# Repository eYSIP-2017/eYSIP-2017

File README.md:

# eYSIP-2017_DistributedRobotics
## Project Title: 
Distributed Robotic - Multi Swarm Robots

## Project Description:
Understanding the behaviour of swarm robots and swarm intelligence. Building of swarm robots and displaying collective intelligence.

## Problem definition:
Using the swarm robots make the desired shapes of Alphabets. 

## Team: 
### Mentors: 
Ms. Rutuja and Ms. Deepa
### Members: 
Mr. R Hariharan and Mr. Chinmay

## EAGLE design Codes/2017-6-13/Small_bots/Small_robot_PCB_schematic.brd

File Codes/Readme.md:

# Contents of the folder
2017-5-27 : P-Controller for angular velocity of a robot (C Code)

2017-5-30 : C Code for Randezvous Problem 

2017-5-31 : Embedded C Code for Randezvous Problem (Firebird V)

2017-6-01 : Mini Bots eagle design folder and line forming algorithm C Code

2017-6-07 : Mini Bots eagle design folder - Updated

2017-6-09 : Mini Bots eagle design folder - Updated

2017-6-10 : Embedded C Code to check the properties of switching IR (Firebird V)

2017-6-13 : Mini Bots eagle design folder - Updated

2017-6-19 : V-REP documents for P-Controller for a mobile robot to goto any co-ordinate

2017-6-26 : V-REP documents for implementation of circle formation of fat robots algorithm
 
2017-6-27 : All the test codes for our Mini Robot

2017-7-05 : V-REP documents for implementation generic shape formation algorithm

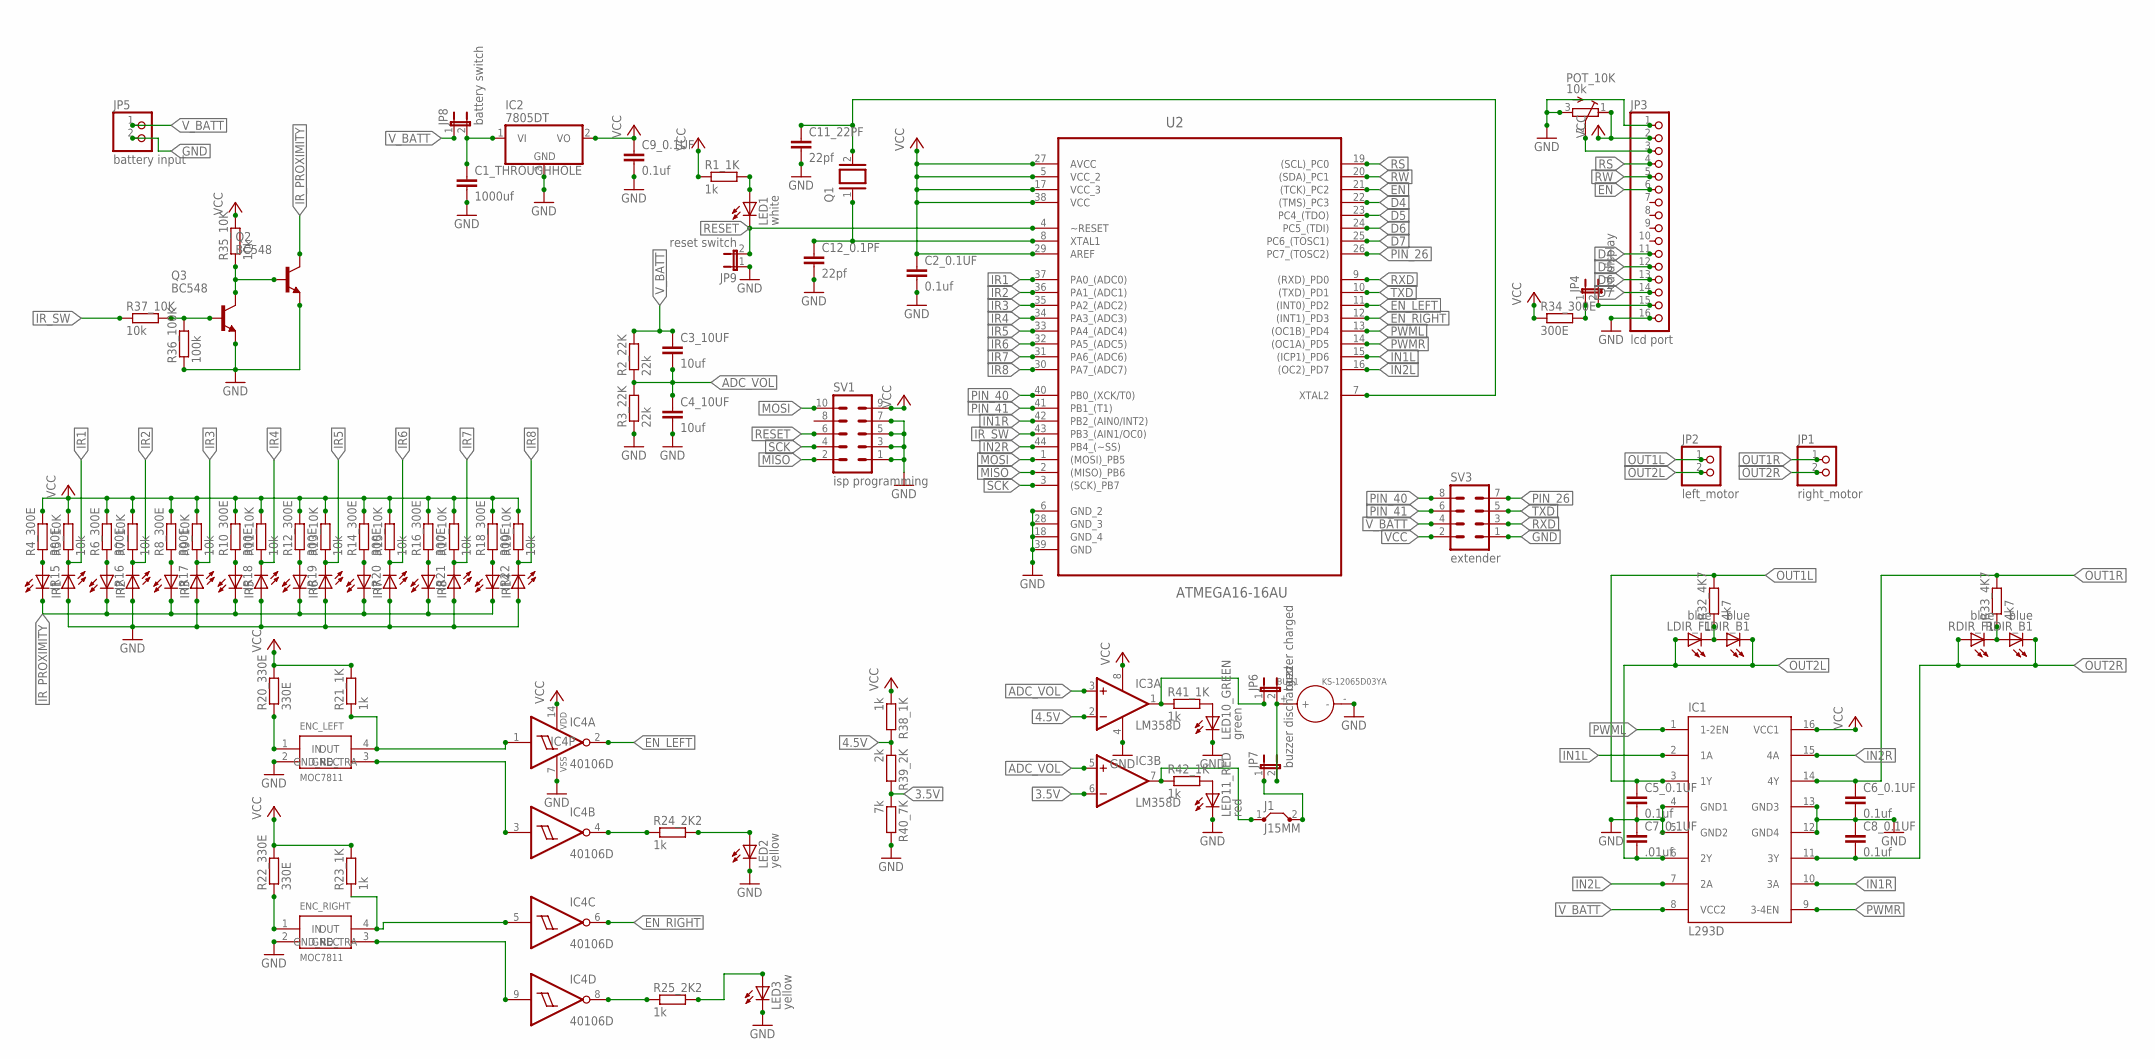
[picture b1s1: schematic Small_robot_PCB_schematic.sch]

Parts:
BUZ1: KS-12065D03YA; BZ2-7.6-D12.0XH6.5MM
C1_THROUGHHOLE: 1000uf; C050-045X075
C2_0.1UF, C5_0.1UF, C6_0.1UF, C8_0.1UF, C9_0.1UF: 0.1uf; C1206
C3_10UF, C4_10UF: 10uf; C1206
C7_0.1UF: .01uf; C1206
C11_22PF, C12_0.1PF: 22pf; C1206
ENC_LEFT: MOC7811; THROUGH_HOLE_NORMAL
ENC_RIGHT: MOC7811; THROUGH_HOLE_NORMAL
IC1: L293D; DIL16
IC2: 7805DT; TO252
IC3: LM358D; SO08
IC4: 40106D; SO14
IR1, IR2, IR3, IR5, IR6, IR7, IR8, IR14, IR15, IR16, IR17, IR18, IR19, IR20, IR21, IR22: LED5MM
J1: J15MM; 15
JP1: right_motor; 1X02
JP2: left_motor; 1X02
JP3: lcd port; 1X16
JP4: lcd display; JP1
JP5: battery input; 1X02
JP6: buzzer charged; JP1
JP7: buzzer discharged; JP1
JP8: battery switch; JP1
JP9: reset switch; JP1
LDIR_B1: blue; CHIPLED_1206
LDIR_F1: blue; CHIPLED_1206
LED1: white; CHIPLED_1206
LED2, LED3: yellow; CHIPLED_1206
LED10_GREEN: green; CHIPLED_1206
LED11_RED: red; CHIPLED_1206
POT_10K: 10k; RTRIMT93YA
Q1: XTAL; Q
Q2, Q3: BC548; TO92-EBC
R1_1K, R21_1K, R23_1K, R24_2K2, R25_2K2, R38_1K, R41_1K, R42_1K: 1k; R1206
R2_22K, R3_22K: 22k; R1206
R4_300E, R6_300E, R8_300E, R10_300E, R12_300E, R14_300E, R16_300E, R18_300E, R34_300E: 300E; R1206
R5_10K, R7_10K, R9_10K, R11_10K, R13_10K, R15_10K, R17_10K, R19_10K, R35_10K, R37_10K: 10k; R1206
R20_330E, R22_330E: 330E; R1206
R32_4K7, R33_4K7: 4k7; R1206
R36_100K: 100k; R1206
R39_2K: 2k; R1206
R40_7K: 7k; R1206
RDIR_B1: blue; CHIPLED_1206
RDIR_F1: blue; CHIPLED_1206
SV1: isp programming; MA05-2
SV3: extender; MA04-2
U2: ATMEGA16-16AU; QFP80P1200X1200X120-44N

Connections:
3.5V: IC3.6 (-IN), R39_2K.2, R40_7K.1
4.5V: IC3.2 (-IN), R38_1K.2, R39_2K.1
ADC_VOL: C3_10UF.2, C4_10UF.1, IC3.3 (+IN), IC3.5 (+IN), R2_22K.1, R3_22K.2
D4: JP3.11, U2.22 ((TMS)_PC3)
D5: JP3.12, U2.23 (PC4_(TDO))
D6: JP3.13, U2.24 (PC5_(TDI))
D7: JP3.14, U2.25 (PC6_(TOSC1))
EN: JP3.6, U2.21 ((TCK)_PC2)
EN_LEFT: IC4.2 (O), U2.11 ((INT0)_PD2)
EN_RIGHT: IC4.6 (O), U2.12 ((INT1)_PD3)
GND: BUZ1.-, C1_THROUGHHOLE.2, C2_0.1UF.2, C4_10UF.2, C5_0.1UF.2, C6_0.1UF.2, C7_0.1UF.1, C8_0.1UF.1, C9_0.1UF.2, C11_22PF.2, C12_0.1PF.2, ENC_LEFT.2 (GND_TRA), ENC_RIGHT.2 (GND_TRA), IC1.4 (GND1), IC1.5 (GND2), IC1.12 (GND4), IC1.13 (GND3), IC2.3 (GND), IC3.4 (V-), IC4.7 (VSS), IR15.A, IR16.A, IR17.A, IR18.A, IR19.A, IR20.A, IR21.A, IR22.A, JP3.1, JP3.16, JP5.2, JP9.1, LED2.C, LED3.C, LED10_GREEN.C, LED11_RED.C, POT_10K.3 (A), Q2.E, Q3.E, R3_22K.1, R36_100K.1, R40_7K.2, SV1.1, SV1.3, SV1.5, SV1.7, SV3.1, U2.6 (GND_2), U2.18 (GND_4), U2.28 (GND_3), U2.39 (GND)
IN1L: IC1.2 (1A), U2.15 ((ICP1)_PD6)
IN1R: IC1.10 (3A), U2.42 (PB2_(AIN0/INT2))
IN2L: IC1.7 (2A), U2.16 ((OC2)_PD7)
IN2R: IC1.15 (4A), U2.44 (PB4_(~SS))
IR1: IR15.K (C), R5_10K.1, U2.37 (PA0_(ADC0))
IR2: IR16.K (C), R7_10K.1, U2.36 (PA1_(ADC1))
IR3: IR17.K (C), R9_10K.1, U2.35 (PA2_(ADC2))
IR4: IR18.K (C), R11_10K.1, U2.34 (PA3_(ADC3))
IR5: IR19.K (C), R13_10K.1, U2.33 (PA4_(ADC4))
IR6: IR20.K (C), R15_10K.1, U2.32 (PA5_(ADC5))
IR7: IR21.K (C), R17_10K.1, U2.31 (PA6_(ADC6))
IR8: IR22.K (C), R19_10K.1, U2.30 (PA7_(ADC7))
IR_PROXIMITY: IR1.K (C), IR2.K (C), IR3.K (C), IR5.K (C), IR6.K (C), IR7.K (C), IR8.K (C), IR14.K (C), Q2.C
IR_SW: R37_10K.1, U2.43 (PB3_(AIN1/OC0))
MISO: SV1.2, U2.2 ((MISO)_PB6)
MOSI: SV1.10, U2.1 ((MOSI)_PB5)
N: JP3.3, POT_10K.2 (S)
unnamed: ENC_LEFT.1 (IN), R20_330E.1
unnamed: C12_0.1PF.1, Q1.1, U2.8 (XTAL1)
unnamed: C11_22PF.1, Q1.2, U2.7 (XTAL2)
unnamed: IR1.A, R4_300E.1
unnamed: IR2.A, R6_300E.1
unnamed: IR3.A, R8_300E.1
unnamed: IR5.A, R10_300E.1
unnamed: LED1.A, R1_1K.2
unnamed: IR6.A, R12_300E.1
unnamed: IR7.A, R14_300E.1
unnamed: IR8.A, R16_300E.1
unnamed: IR14.A, R18_300E.1
unnamed: Q3.B, R36_100K.2, R37_10K.2
unnamed: C1_THROUGHHOLE.1, IC2.1 (VI), JP8.2
unnamed: IC4.4 (O), R24_2K2.1
unnamed: LED2.A, R24_2K2.2
unnamed: IC4.8 (O), R25_2K2.1
unnamed: LED3.A, R25_2K2.2
unnamed: ENC_RIGHT.1 (IN), R22_330E.1
unnamed: LED10_GREEN.A, R41_1K.2
unnamed: IC3.7 (OUT), J1.1, R42_1K.1
unnamed: ENC_RIGHT.4 (OUT), IC4.5 (I), R23_1K.1
unnamed: J1.2, JP7.1
unnamed: Q2.B, Q3.C, R35_10K.1
unnamed: R33_4K7.1, RDIR_B1.A, RDIR_F1.C
unnamed: ENC_LEFT.4 (OUT), IC4.1 (I), R21_1K.1
unnamed: ENC_LEFT.3 (GND_REC), IC4.3 (I)
unnamed: ENC_RIGHT.3 (GND_REC), IC4.9 (I)
unnamed: LED11_RED.A, R42_1K.2
unnamed: BUZ1.+, JP6.2, JP7.2
unnamed: IC3.1 (OUT), JP6.1, R41_1K.1
unnamed: LDIR_B1.A, LDIR_F1.C, R32_4K7.1
unnamed: JP3.15, JP4.2
unnamed: JP4.1, R34_300E.2
OUT1L: C5_0.1UF.1, IC1.3 (1Y), JP2.1, R32_4K7.2
OUT1R: C6_0.1UF.1, IC1.14 (4Y), JP1.1, R33_4K7.2
OUT2L: C7_0.1UF.2, IC1.6 (2Y), JP2.2, LDIR_B1.C, LDIR_F1.A
OUT2R: C8_0.1UF.2, IC1.11 (3Y), JP1.2, RDIR_B1.C, RDIR_F1.A
PIN_26: SV3.7, U2.26 (PC7_(TOSC2))
PIN_40: SV3.8, U2.40 (PB0_(XCK/T0))
PIN_41: SV3.6, U2.41 (PB1_(T1))
PWML: IC1.1 (1-2EN), U2.13 ((OC1B)_PD4)
PWMR: IC1.9 (3-4EN), U2.14 ((OC1A)_PD5)
RESET: JP9.2, LED1.C, SV1.6, U2.4 (~RESET)
RS: JP3.4, U2.19 ((SCL)_PC0)
RW: JP3.5, U2.20 ((SDA)_PC1)
RXD: SV3.3, U2.9 ((RXD)_PD0)
SCK: SV1.4, U2.3 ((SCK)_PB7)
TXD: SV3.5, U2.10 ((TXD)_PD1)
VCC: C2_0.1UF.1, C9_0.1UF.1, IC1.16 (VCC1), IC2.2 (VO), IC3.8 (V+), IC4.14 (VDD), JP3.2, POT_10K.1 (E), R1_1K.1, R4_300E.2, R5_10K.2, R6_300E.2, R7_10K.2, R8_300E.2, R9_10K.2, R10_300E.2, R11_10K.2, R12_300E.2, R13_10K.2, R14_300E.2, R15_10K.2, R16_300E.2, R17_10K.2, R18_300E.2, R19_10K.2, R20_330E.2, R21_1K.2, R22_330E.2, R23_1K.2, R34_300E.1, R35_10K.2, R38_1K.1, SV1.9, SV3.2, U2.5 (VCC_2), U2.17 (VCC_3), U2.27 (AVCC), U2.29 (AREF), U2.38 (VCC)
V_BATT: C3_10UF.1, IC1.8 (VCC2), JP5.1, JP8.1, R2_22K.2, SV3.4

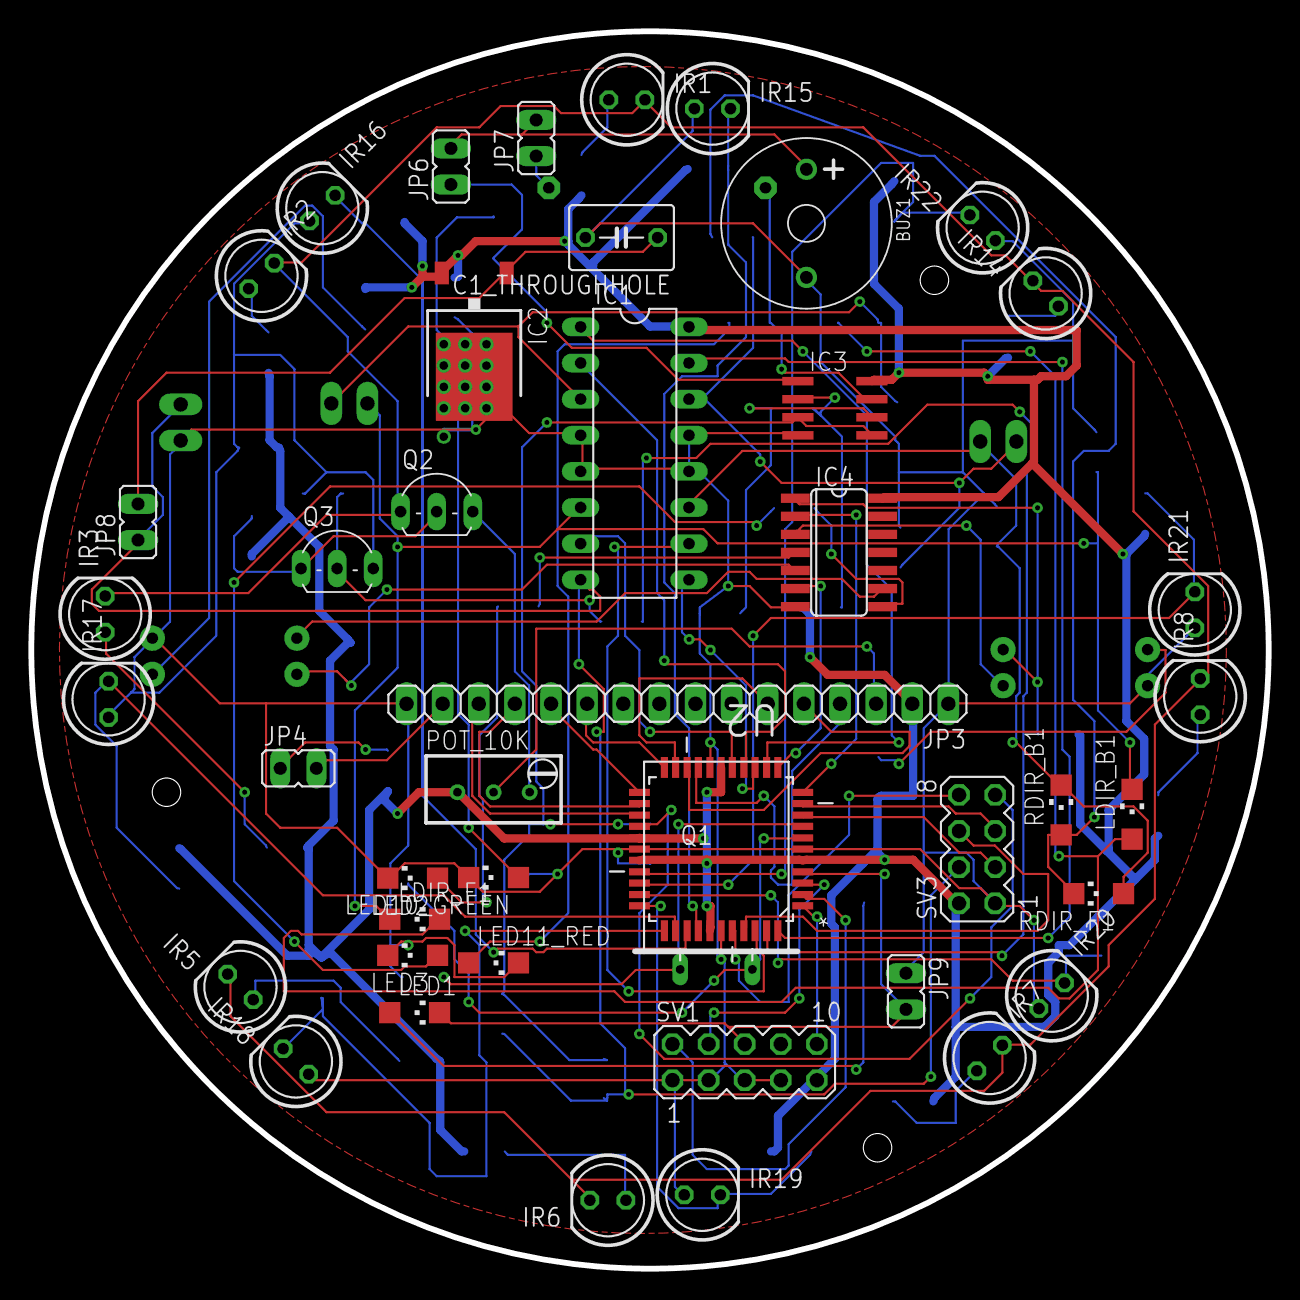
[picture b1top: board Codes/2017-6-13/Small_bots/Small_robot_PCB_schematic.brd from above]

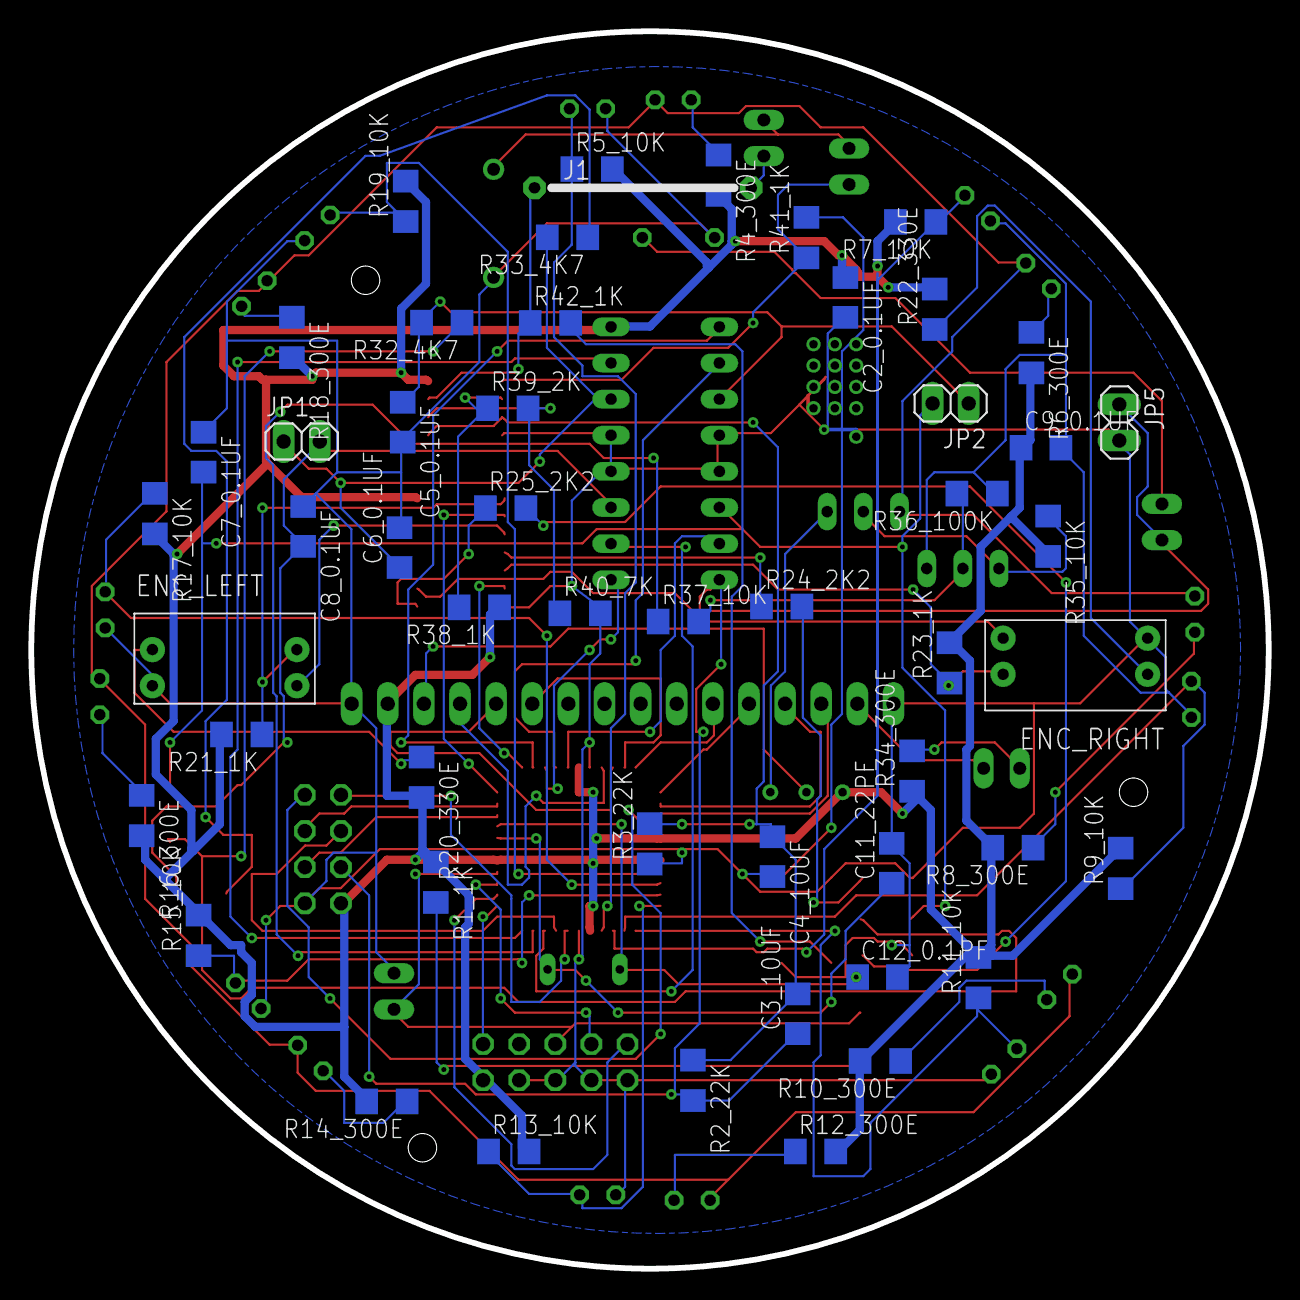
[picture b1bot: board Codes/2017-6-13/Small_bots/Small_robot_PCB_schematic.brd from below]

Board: 2 copper layers, 87.0 x 87.0 mm, 96 parts (52 on the bottom side), 79 nets.

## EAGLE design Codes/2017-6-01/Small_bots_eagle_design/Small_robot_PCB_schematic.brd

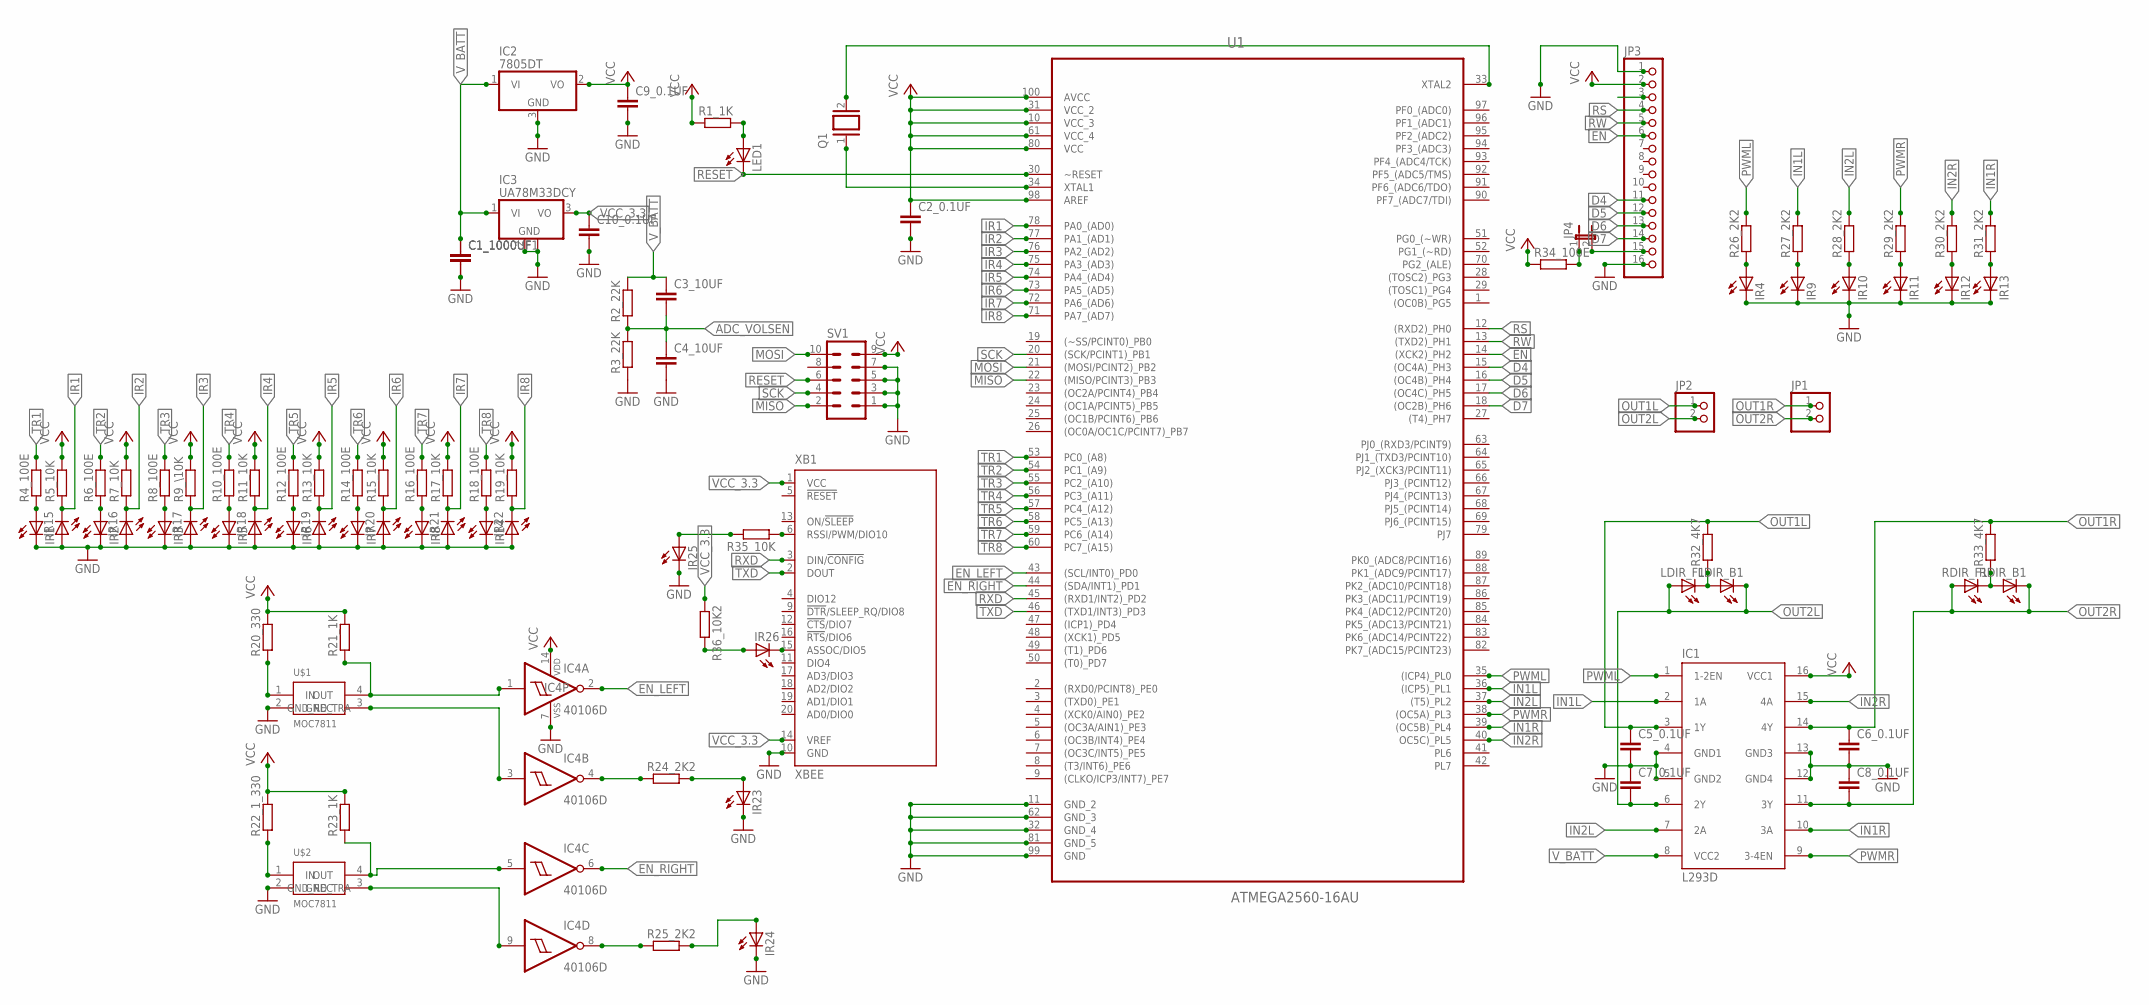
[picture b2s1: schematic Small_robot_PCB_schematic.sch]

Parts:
C1_1000UF, C1_1000UF1, C2_0.1UF, C3_10UF, C4_10UF, C5_0.1UF, C6_0.1UF, C7_0.1UF, C8_0.1UF, C9_0.1UF, C10_0.1UF: C-EUC1206; C1206
IC1: L293D; DIL16
IC2: 7805DT; TO252
IC3: UA78M33DCY; SOT223
IC4: 40106D; SO14
IR1, IR2, IR3, IR5, IR6, IR7, IR8, IR14, IR15, IR16, IR17, IR18, IR19, IR20, IR21, IR22: LED5MM
IR4, IR9, IR10, IR11, IR12, IR13, IR23, IR24, IR25, IR26: LEDCHIPLED_1206; CHIPLED_1206
JP1, JP2: PINHD-1X2; 1X02
JP3: PINHD-1X16; 1X16
JP4: JP1E; JP1
LDIR_B1: LEDCHIPLED_1206; CHIPLED_1206
LDIR_F1: LEDCHIPLED_1206; CHIPLED_1206
LED1: LEDCHIPLED_1206; CHIPLED_1206
Q1: XTAL; Q
R1_1K, R2_22K, R4_100E, R5_10K, R6_100E, R7_10K, R8_100E, R9_\10K, R10_100E, R11_10K, R12_100E, R13_10K, R14_100E, R15_10K, R16_100E, R17_10K, R18_100E, R19_10K, R20_330, R21_1K, R22_1_330, R23_1K, R24_2K2, R25_2K2, R26_2K2, R27_2K2, R28_2K2, R29_2K2, R30_2K2, R31_2K2, R32_4K7, R33_4K7, R34_100E, R35_10K, R36_10K2: R-EU_R1206; R1206
R3_22K: R-EU_M1206; M1206
RDIR_B1: LEDCHIPLED_1206; CHIPLED_1206
RDIR_F1: LEDCHIPLED_1206; CHIPLED_1206
SV1: MA05-2
U1: ATMEGA2560-16AU; QFP50P1600X1600X120-100N
U$1, U$2: MOC7811; THROUGH_HOLE_NORMAL
XB1: XBEE

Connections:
ADC_VOLSEN: C3_10UF.2, C4_10UF.1, R2_22K.1, R3_22K.2
D4: JP3.11, U1.15 ((OC4A)_PH3)
D5: JP3.12, U1.16 ((OC4B)_PH4)
D6: JP3.13, U1.17 ((OC4C)_PH5)
D7: JP3.14, U1.18 ((OC2B)_PH6)
EN: JP3.6, U1.14 ((XCK2)_PH2)
EN_LEFT: IC4.2 (O), U1.43 ((SCL/INT0)_PD0)
EN_RIGHT: IC4.6 (O), U1.44 ((SDA/INT1)_PD1)
GND: C1_1000UF.2, C1_1000UF1.2, C2_0.1UF.2, C4_10UF.2, C5_0.1UF.2, C6_0.1UF.2, C7_0.1UF.1, C8_0.1UF.1, C9_0.1UF.2, C10_0.1UF.2, IC1.4 (GND1), IC1.5 (GND2), IC1.12 (GND4), IC1.13 (GND3), IC2.3 (GND), IC3.2 (GND), IC3.4 (GND), IC4.7 (VSS), IR1.K (C), IR2.K (C), IR3.K (C), IR4.C, IR5.K (C), IR6.K (C), IR7.K (C), IR8.K (C), IR9.C, IR10.C, IR11.C, IR12.C, IR13.C, IR14.K (C), IR15.A, IR16.A, IR17.A, IR18.A, IR19.A, IR20.A, IR21.A, IR22.A, IR23.C, IR24.C, IR25.C, JP3.1, JP3.16, R3_22K.1, SV1.1, SV1.3, SV1.5, SV1.7, U1.11 (GND_2), U1.32 (GND_4), U1.62 (GND_3), U1.81 (GND_5), U1.99 (GND), U$1.2 (GND_TRA), U$2.2 (GND_TRA), XB1.10 (GND)
IN1L: IC1.2 (1A), R27_2K2.2, U1.36 ((ICP5)_PL1)
IN1R: IC1.10 (3A), R31_2K2.2, U1.39 ((OC5B)_PL4)
IN2L: IC1.7 (2A), R28_2K2.2, U1.37 ((T5)_PL2)
IN2R: IC1.15 (4A), R30_2K2.2, U1.40 (OC5C)_PL5)
IR1: IR15.K (C), R5_10K.1, U1.78 (PA0_(AD0))
IR2: IR16.K (C), R7_10K.1, U1.77 (PA1_(AD1))
IR3: IR17.K (C), R9_\10K.1, U1.76 (PA2_(AD2))
IR4: IR18.K (C), R11_10K.1, U1.75 (PA3_(AD3))
IR5: IR19.K (C), R13_10K.1, U1.74 (PA4_(AD4))
IR6: IR20.K (C), R15_10K.1, U1.73 (PA5_(AD5))
IR7: IR21.K (C), R17_10K.1, U1.72 (PA6_(AD6))
IR8: IR22.K (C), R19_10K.1, U1.71 (PA7_(AD7))
MISO: SV1.2, U1.22 ((MISO/PCINT3)_PB3)
MOSI: SV1.10, U1.21 ((MOSI/PCINT2)_PB2)
N: JP3.3
unnamed: R20_330.1, U$1.1 (IN)
unnamed: Q1.1, U1.34 (XTAL1)
unnamed: Q1.2, U1.33 (XTAL2)
unnamed: IR1.A, R4_100E.1
unnamed: IR2.A, R6_100E.1
unnamed: IR3.A, R8_100E.1
unnamed: IR5.A, R10_100E.1
unnamed: LED1.A, R1_1K.2
unnamed: IR6.A, R12_100E.1
unnamed: IR7.A, R14_100E.1
unnamed: IR8.A, R16_100E.1
unnamed: IR14.A, R18_100E.1
unnamed: IR4.A, R26_2K2.1
unnamed: IC4.4 (O), R24_2K2.1
unnamed: IR23.A, R24_2K2.2
unnamed: IC4.8 (O), R25_2K2.1
unnamed: IR24.A, R25_2K2.2
unnamed: R22_1_330.1, U$2.1 (IN)
unnamed: IR9.A, R27_2K2.1
unnamed: IR10.A, R28_2K2.1
unnamed: IC4.5 (I), R23_1K.1, U$2.4 (OUT)
unnamed: IR11.A, R29_2K2.1
unnamed: IR12.A, R30_2K2.1
unnamed: IR13.A, R31_2K2.1
unnamed: R35_10K.1, XB1.6 (RSSI/PWM/DIO10)
unnamed: R33_4K7.1, RDIR_B1.A, RDIR_F1.C
unnamed: IC4.1 (I), R21_1K.1, U$1.4 (OUT)
unnamed: IC4.3 (I), U$1.3 (GND_REC)
unnamed: IC4.9 (I), U$2.3 (GND_REC)
unnamed: IR25.A, R35_10K.2
unnamed: IR26.C, XB1.15 (ASSOC/DIO5)
unnamed: IR26.A, R36_10K2.2
unnamed: LDIR_B1.A, LDIR_F1.C, R32_4K7.1
unnamed: JP3.15, JP4.2
unnamed: JP4.1, R34_100E.2
OUT1L: C5_0.1UF.1, IC1.3 (1Y), JP2.1, R32_4K7.2
OUT1R: C6_0.1UF.1, IC1.14 (4Y), JP1.1, R33_4K7.2
OUT2L: C7_0.1UF.2, IC1.6 (2Y), JP2.2, LDIR_B1.C, LDIR_F1.A
OUT2R: C8_0.1UF.2, IC1.11 (3Y), JP1.2, RDIR_B1.C, RDIR_F1.A
PWML: IC1.1 (1-2EN), R26_2K2.2, U1.35 ((ICP4)_PL0)
PWMR: IC1.9 (3-4EN), R29_2K2.2, U1.38 ((OC5A)_PL3)
RESET: LED1.C, SV1.6, U1.30 (~RESET)
RS: JP3.4, U1.12 ((RXD2)_PH0)
RW: JP3.5, U1.13 ((TXD2)_PH1)
RXD: U1.45 ((RXD1/INT2)_PD2), XB1.3 (DIN/!CONFIG)
SCK: SV1.4, U1.20 ((SCK/PCINT1)_PB1)
TR1: R4_100E.2, U1.53 (PC0_(A8))
TR2: R6_100E.2, U1.54 (PC1_(A9))
TR3: R8_100E.2, U1.55 (PC2_(A10))
TR4: R10_100E.2, U1.56 (PC3_(A11))
TR5: R12_100E.2, U1.57 (PC4_(A12))
TR6: R14_100E.2, U1.58 (PC5_(A13))
TR7: R16_100E.2, U1.59 (PC6_(A14))
TR8: R18_100E.2, U1.60 (PC7_(A15))
TXD: U1.46 ((TXD1/INT3)_PD3), XB1.2 (DOUT)
VCC: C2_0.1UF.1, C9_0.1UF.1, IC1.16 (VCC1), IC2.2 (VO), IC4.14 (VDD), JP3.2, R1_1K.1, R5_10K.2, R7_10K.2, R9_\10K.2, R11_10K.2, R13_10K.2, R15_10K.2, R17_10K.2, R19_10K.2, R20_330.2, R21_1K.2, R22_1_330.2, R23_1K.2, R34_100E.1, SV1.9, U1.10 (VCC_3), U1.31 (VCC_2), U1.61 (VCC_4), U1.80 (VCC), U1.98 (AREF), U1.100 (AVCC)
VCC_3.3: C10_0.1UF.1, IC3.3 (VO), R36_10K2.1, XB1.1 (VCC), XB1.14 (VREF)
V_BATT: C1_1000UF.1, C1_1000UF1.1, C3_10UF.1, IC1.8 (VCC2), IC2.1 (VI), IC3.1 (VI), R2_22K.2

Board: 2 copper layers, 92 parts (0 on the bottom side), 81 nets, no tracks yet.

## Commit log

2017-05-27 2017/05/27-19:00
2017-05-29 Report
2017-05-29 Codes
2017-05-30 Getting Proper Centroid
2017-05-31 Randevous problem code for firebird, Need to map sensor values properly
2017-05-31 Randevous Problem Solved, But need proper sensing values or conversion
2017-05-31 Everything Working fine
2017-06-01 Line Forming working, but not for symmetric structures
2017-06-01 Eagle layout without routing done
2017-06-05 Progress Presentation I
2017-06-05 Progress Presentation 1, with images
2017-06-05 Presentation, IR sensors added properly
2017-06-07 Design of PCB and layout done
2017-06-08 Componet list of PCB requirement
2017-06-09 Final schematic and layout
2017-06-10 IR switching
2017-06-13 Final PCB for manufacturing
2017-06-19 V-REP trail P Controller with model and scene added
2017-06-26 Circle Formation in V-REP completed
2017-06-27 Test codes for small_bots
2017-06-28 Final Poster
2017-07-05 PID code commented
2017-07-05 Rendezous Problem
2017-07-05 Removed
2017-07-05 Removed Video
2017-07-05 Rendezous problem C program commented
2017-07-05 Firebird V Rendezous code commented
2017-07-05 Line Forming Code commented
2017-07-05 P Controller Code Commented
2017-07-05 V-REP Readme
2017-07-05 Circle Formation code Commented
2017-07-05 Shape formation
2017-07-05 documentation uploaded for editing
2017-07-05 Generic shape formation alogorithm
2017-07-05 Documents edited but not finalized
2017-07-05 Understanding V-REP for Beginners
2017-07-05 Generc shape formation algorithm implementation code
2017-07-05 V-REP Generic Shape formation Readme
2017-07-06 Added Section and chapters
2017-07-06 Report finalized, hardwre manual yet to be finalized
2017-07-07 Remover Project Report
2017-07-07 Readme for codes to explain the structure
2017-07-07 Final documents
